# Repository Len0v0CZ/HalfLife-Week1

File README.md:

# Macro Keyboard

A compact macro keyboard featuring 3 keys and 1 rotary encoder for task automation.
## Components
- Raspberry Pi Pico
- 3x Mechanical Switches
- 1x KY-040 Rotary Encoder
- Custom PCB
- 3D-printed case (base and lid)

## Hardware Assembly
1. Solder the Pico, switches, and encoder to the PCB.
2. Mount the assembled PCB into the 3D-printed base using the M3 sized studs.
3. Attach the lid.

## Software Setup
1. Install CircuitPython on the Raspberry Pi Pico, more precisely it uses `adafruit_hid` library.
2. Save the Python script as `code.py` in the root directory.

## Usage
The rotary encoder adjusts the system volume and its button toggles mute. The three mechanical switches can be bound in `code.py`.

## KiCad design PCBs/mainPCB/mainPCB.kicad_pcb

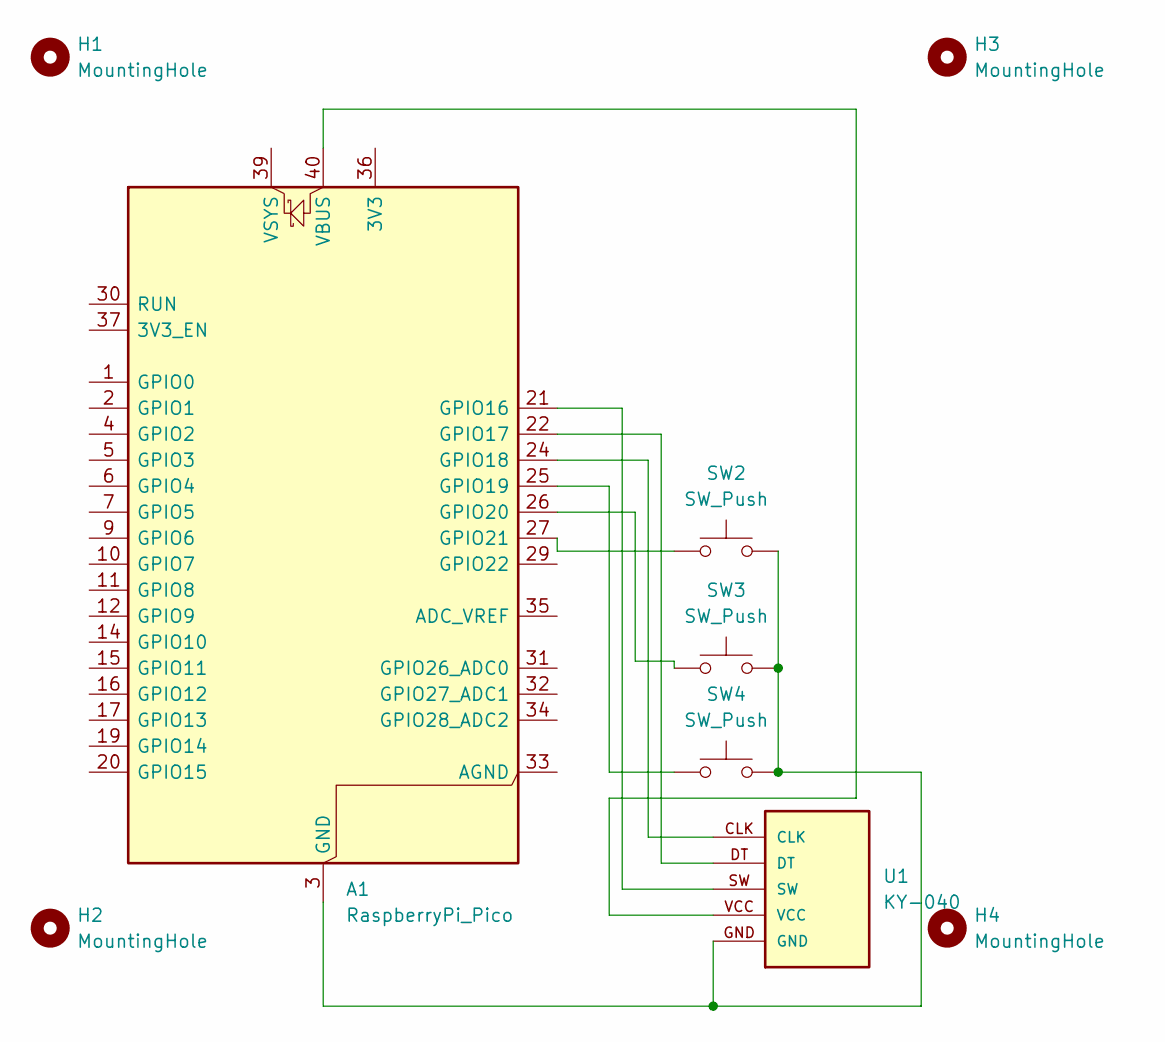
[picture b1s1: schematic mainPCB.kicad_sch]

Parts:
A1: RaspberryPi_Pico; RaspberryPi_Pico_Common_Unspecified
H1, H2, H3, H4: MountingHole; MountingHole_3.2mm_M3_DIN965
SW2, SW3, SW4: SW_Push; SW_Cherry_MX_1.00u_Plate
U1: KY-040; KY-040-PORT

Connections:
unnamed: A1.3 (GND), A1.8 (GND), A1.13 (GND), A1.18 (GND), A1.23 (GND), A1.28 (GND), A1.38 (GND), SW2.2, SW3.2, SW4.2, U1.GND
unnamed: A1.21 (GPIO16), U1.SW
unnamed: A1.22 (GPIO17), U1.DT
unnamed: A1.24 (GPIO18), U1.CLK
unnamed: A1.25 (GPIO19), SW4.1
unnamed: A1.26 (GPIO20), SW3.1
unnamed: A1.27 (GPIO21), SW2.1
unnamed: A1.40 (VBUS), U1.VCC

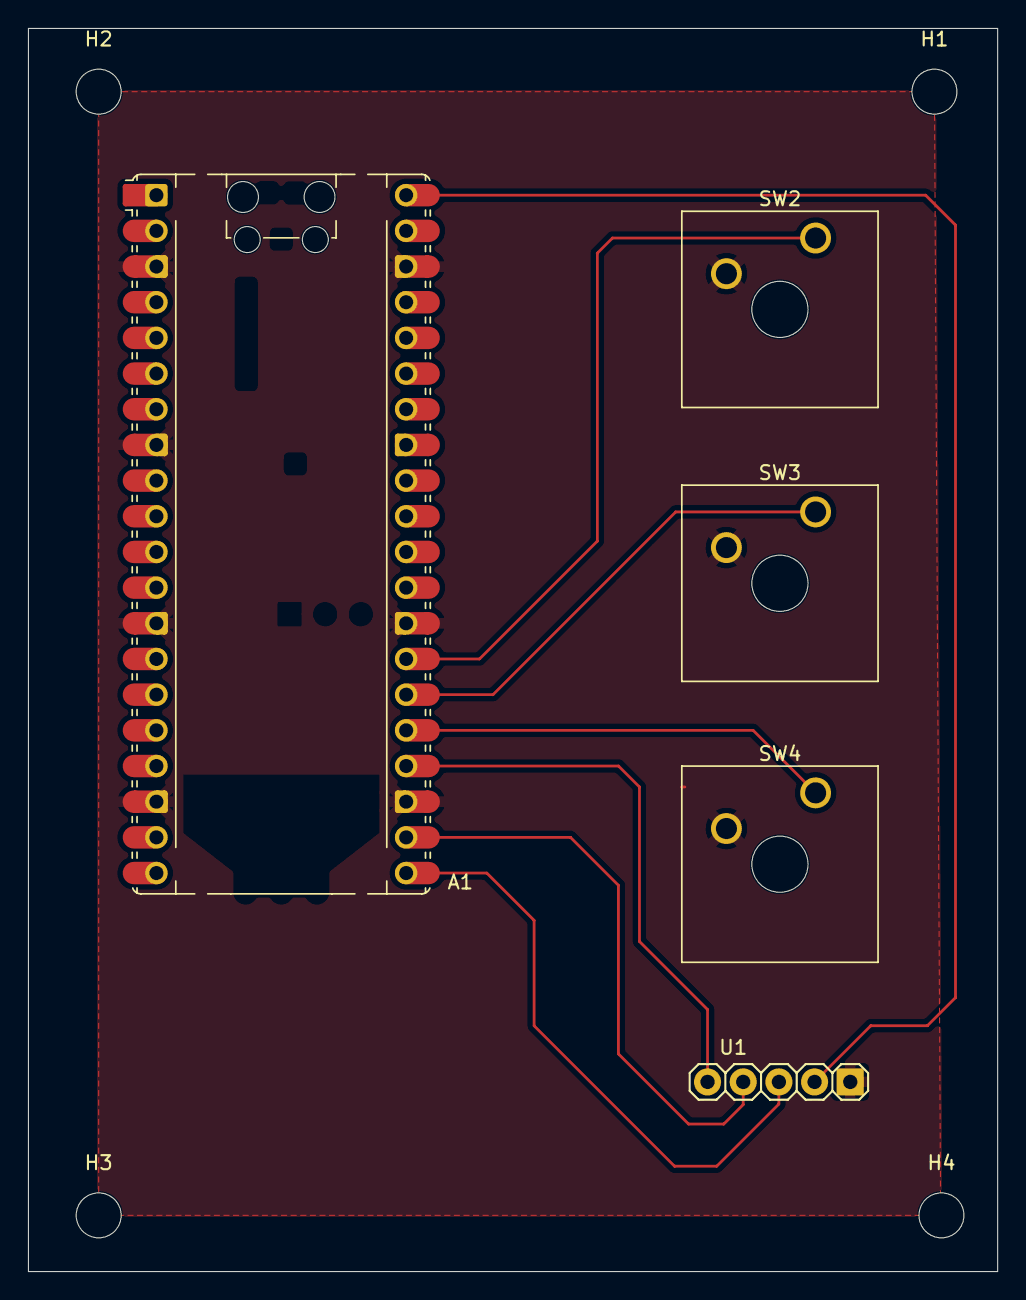
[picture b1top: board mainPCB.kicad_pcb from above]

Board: 2 copper layers, 69.0 x 88.5 mm, 9 parts (0 on the bottom side), 8 nets.
